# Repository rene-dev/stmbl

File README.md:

Build Log: https://travis-ci.org/rene-dev/stmbl

DISCLAIMER
===

THE AUTHORS OF THIS SOFTWARE ACCEPT ABSOLUTELY NO LIABILITY FOR
ANY HARM OR LOSS RESULTING FROM ITS USE.  IT IS _EXTREMELY_ UNWISE
TO RELY ON SOFTWARE ALONE FOR SAFETY.  Any machinery capable of
harming persons must have provisions for completely removing power
from all motors, etc, before persons enter any danger area.  All
machinery must be designed to comply with local and national safety
codes, and the authors of this software can not, and do not, take
any responsibility for such compliance.

This software is released under the GPLv3.

STMBL
=====
There is work in progress on documentation: https://github.com/rene-dev/stmbl/blob/master/docs/src/Getting%20Started.adoc

**IRC: #stmbl on irc.hackint.eu**
https://webirc.hackint.org/#stmbl

STMBL is an open source servo drive designed for Retrofitting CNC machines and Robots. It supports Industrial AC and DC servos with up to 320V and 2kW (see [specs](https://github.com/rene-dev/stmbl/wiki/specs) for details).

Documentation about the PCB and pinout of the feedback connector:

https://github.com/rene-dev/stmbl/wiki/Pinouts

https://github.com/rene-dev/stmbl/wiki/PCB

##### Hardware version 4.1

##### Driving a Bosch Turboscara
https://www.youtube.com/watch?v=d6NH1W7DUnQ  
https://www.youtube.com/watch?v=oTllxnYAgFc

##### Driving a Manutec Robot
https://www.youtube.com/watch?v=gwgnAeGjZrA  
https://www.youtube.com/watch?v=wXLcAZwjlzE

##### Driving a Weeke BP12 VMC
https://www.youtube.com/watch?v=24LftGNp4MI

##### Driving a Haas VF0 (Spindle + Axes)
https://www.youtube.com/watch?v=kqenepupJIs

##### Drivetest
https://www.youtube.com/watch?v=-E1o_5cFyto

#### Supported Motors
* Synchronous AC Servos
* Asynchronous AC Servos
* DC Servos
* 2 Phase HF spindle motors

#### Supported Feedback systems
* Resolvers
* Incremental encoders
* sin/cos encoder interpolation
* Mitsubishi absolute encoders
* Sanyo Denki absolute encoders
* Yaskawa absolute encoders
* Sick HIPERFACE®
* Tamagawa SmartAbs

##### Planned:
* EnDat
* BiSS
* SSI
* Sanyo Denki wire-saving incremental encoder

#### Supported Position/Velocity Commands Inputs:
* Smartserial
* Quadrature
* Step/direction
* RS485

#### TODO
* Sensorless FOC

#### Directories
* [hw/spice/](hw/spice/) Spice simulation for resolver interface
* [hw/kicad/v4.0/](hw/kicad/v4.0/) kicad files for version 4
* [src/](src/) STM32F4 code, command, feedback and control loop
* [stm32f303/](stm32f303/) STM32F3 code, running on the HV side, generating PWM

##### Commercial Applications

Should you find the GPL license insufficient for your needs, other licenses
can be purchased from my company.

Likewise, please contact us should you wish to fund the further development
of this project, or are interesed in custom hardware, software, or commercial support.

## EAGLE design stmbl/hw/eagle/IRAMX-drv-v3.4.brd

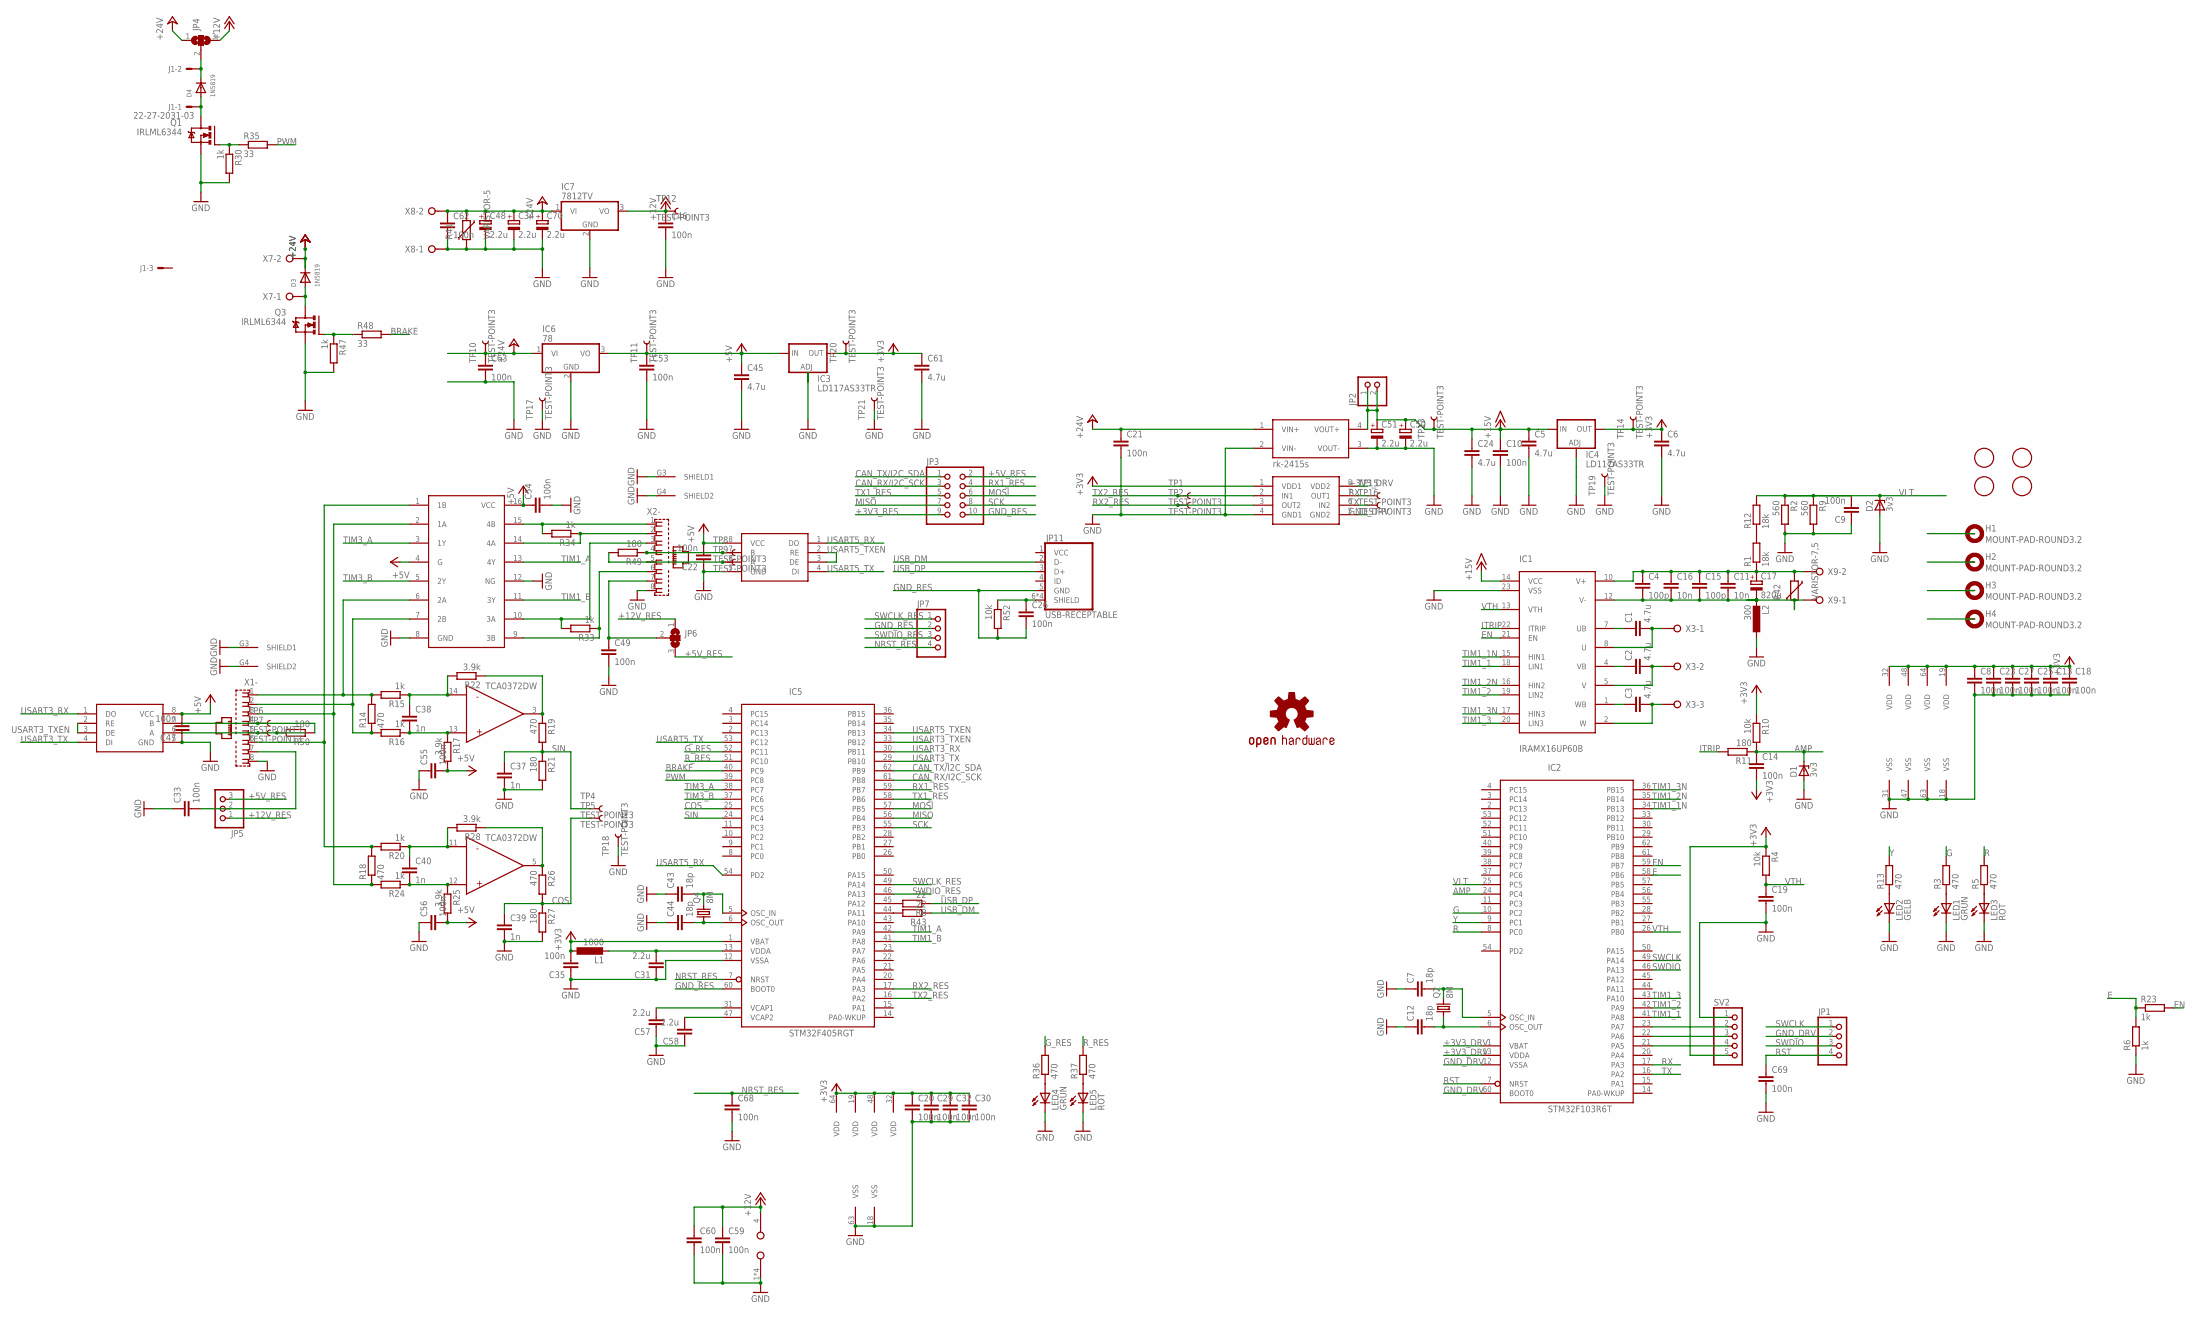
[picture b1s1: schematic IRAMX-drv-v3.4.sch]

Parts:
C1, C2, C3, C5, C6, C24, C45, C61: 4.7u; C0805
C4, C15: 100p; C1206K
C7, C12, C43, C44: 18p; C0603
C8, C9, C10, C13, C14, C18, C19, C20, C21, C22, C23, C25, C26, C27, C29, C30, C32, C33, C35, C46, C47, C49, C53, C54, C55, C56, C59, C60, C62, C63, C68, C69: 100n; C0603
C11, C16: 10n; C1206K
C17: 820µ; EB35D
C31, C57, C58: 2.2u; C0603
C34, C50, C70: 2.2u; 153CLV-0405
C37, C38, C39, C40: 1n; C0603
C48, C51: 2.2u; E2,5-6E
D1, D2: 3v3; SOD80C
D3, D4: 1N5819; SOD-123
H1, H2, H3, H4: MOUNT-PAD-ROUND3.2; 3,2-PAD
IC1: IRAMX16UP60B; SIP23_TOP
IC2: STM32F103R6T; LQFP64
IC3, IC4: LD117AS33TR; SOT223
IC5: STM32F405RGT; LQFP64
IC6: 78; R-78E
IC7: 7812TV; TO220V
IC8, IC9: ADM485SOIC8; SOIC08
IC10: TCA0372DWDM2; TCA0372DM2
IC12: SI8621; SOIC08
IC13: AM26LS32ACD; SO16
IC14: rk-2415s; SIP7
J1: 22-27-2031-03; 6410-03
JP1, JP7: PINHD-1X4; 1X04
JP2: PINHD-1X2; 1X02
JP3: PINHD-2X5; 2X05
JP4, JP6: SJ2W; SJ_2
JP5: PINHD-1X3; 1X03
JP11: USB-RECEPTABLE; FCI-10103594-0001LF
L1: 1000; L2825P
L2: 300; L2825P
LED1, LED4: GRÜN; LED3MM
LED2: GELB; LED3MM
LED3, LED5: ROT; LED3MM
LOGO1: OSHW-LOGOL; OSHW-LOGO-L
Q1, Q3: IRLML6344; MICRO3
Q2, Q4: 8M; CTS406
R1, R12: 18k; CER
R2, R9: 560; R0805
R3, R5, R13, R14, R18, R19, R26, R36, R37: 470; R0603
R4, R10, R52: 10k; R0603
R6, R15, R16, R20, R23, R24, R30, R33, R34, R47: 1k; R0603
R8, R43: 22; R0603
R11, R21, R27, R49, R50: 180; R0603
R17, R22, R25, R28: 3.9k; R0603
R35, R48: 33; R0603
R41: VARISTOR-5; R-5
R42: VARISTOR-7,5; R-7,5
SV2: PINHD-1X5; 1X05
TP1, TP2, TP4, TP5, TP6, TP7, TP8, TP9, TP10, TP11, TP12, TP13, TP14, TP15, TP16, TP17, TP18, TP19, TP20, TP21: TEST-POINT3; PAD.03X.03
U$8, U$9, U$10, U$11: FIDUCIAL; FIDUCIAL_1MM
X1, X2: RJ45
X3: AKL230-03
X7, X8, X9: AKL230-02

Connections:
+3V3_DRV: C6.1, C8.1, C13.1, C14.2, C18.1, C23.1, C25.1, C27.1, IC2.1 (VBAT), IC2.13 (VDDA), IC2.19 (VDD), IC2.32 (VDD), IC2.48 (VDD), IC2.64 (VDD), IC4.2 (OUT), IC4.4 (OUT), IC12.8 (VDD2), R4.1, R10.1, SV2.5, TP14.P$1
+3V3_RES: C20.1, C29.1, C30.1, C32.1, C35.2, C61.1, IC3.2 (OUT), IC3.4 (OUT), IC5.1 (VBAT), IC5.19 (VDD), IC5.32 (VDD), IC5.48 (VDD), IC5.64 (VDD), IC12.1 (VDD1), JP3.9, L1.1, TP20.P$1
+5V_RES: C22.2, C45.1, C47.2, C53.1, C54.1, C55.2, C56.2, IC3.3 (IN), IC6.3 (VO), IC8.8 (VCC), IC9.8 (VCC), IC13.4 (G), IC13.16 (VCC), JP3.2, JP5.3, JP6.3, R17.2, R25.2, TP11.P$1
+12V_RES: C46.1, C59.1, C60.1, IC7.3 (VO), IC10.4 (VCC), JP4.3, JP5.1, JP6.1, TP12.P$1
+15V_DRV: C5.1, C10.1, C24.1, C50.+, C51.+, IC1.14 (VCC), IC4.3 (IN), IC14.4 (VOUT+), JP2.1, JP2.2, TP13.P$1
+24V_RES: C21.1, C34.+, C48.+, C62.1, C63.1, C70.+, D3.C, IC6.1 (VI), IC7.1 (VI), IC14.1 (VIN+), JP4.1, R41.1, TP10.P$1, X7.2, X8.2
AMP: C14.1, D1.C, IC2.24 (PC4), R10.2, R11.1
BRAKE: IC5.40 (PC9), R48.2
CAN_RX/I2C_SCK: IC5.61 (PB8), JP3.3
CAN_TX/I2C_SDA: IC5.62 (PB9), JP3.1
COS: C39.1, IC5.25 (PC5), R26.2, R27.1, TP5.P$1
E: IC2.58 (PB6), R6.2, R23.1
EN: IC1.21 (EN), IC2.59 (PB7), R23.2
G: IC2.10 (PC2), R3.2
GND_DRV: C5.2, C6.2, C7.1, C8.2, C9.1, C10.2, C12.1, C13.2, C18.2, C19.2, C23.2, C24.2, C25.2, C27.2, C50.-, C51.-, C69.2, D1.A, D2.A, IC1.23 (VSS), IC2.12 (VSSA), IC2.18 (VSS), IC2.31 (VSS), IC2.47 (VSS), IC2.60 (BOOT0), IC2.63 (VSS), IC4.1 (ADJ), IC12.5 (GND2), IC14.3 (VOUT-), JP1.2, L2.1, LED1.K (C), LED2.K (C), LED3.K (C), R2.2, R6.1, R9.2, SV2.1, TP19.P$1
GND_RES: C20.2, C21.2, C22.1, C26.2, C29.2, C30.2, C31.1, C32.2, C33.1, C34.-, C35.1, C37.2, C39.2, C43.1, C44.1, C45.2, C46.2, C47.1, C48.-, C49.2, C53.2, C54.2, C55.1, C56.1, C57.1, C58.1, C59.2, C60.2, C61.2, C62.2, C63.2, C68.2, C70.-, IC3.1 (ADJ), IC5.12 (VSSA), IC5.18 (VSS), IC5.60 (BOOT0), IC5.63 (VSS), IC6.2 (GND), IC7.2 (GND), IC8.5 (GND), IC9.5 (GND), IC10.1 (GND), IC10.8 (GND), IC10.9 (GND), IC10.16 (GND), IC12.4 (GND1), IC13.8 (GND), IC13.12 (NG), IC14.2 (VIN-), JP3.10, JP7.2, JP11.5 (GND), LED4.K (C), LED5.K (C), Q1.2 (S), Q3.2 (S), R21.2, R27.2, R30.2, R41.2, R47.2, R52.2, TP17.P$1, TP18.P$1, TP21.P$1, X1.8, X1.G3 (SHIELD1), X1.G4 (SHIELD2), X2.8, X2.G3 (SHIELD1), X2.G4 (SHIELD2), X8.1
G_RES: IC5.52 (PC11), R36.2
ITRIP: IC1.22 (ITRIP), R11.2
MISO: IC5.56 (PB4), JP3.7
MOSI: IC5.57 (PB5), JP3.6
unnamed: C1.1, IC1.7 (UB)
unnamed: R1.P$2 (2), R12.P$1 (1)
unnamed: C2.1, IC1.4 (VB)
unnamed: C3.1, IC1.1 (WB)
unnamed: LED1.A, R3.1
unnamed: LED3.A, R5.1
unnamed: C7.2, IC2.5 (OSC_IN), Q2.3 (2)
unnamed: LED4.A, R36.1
unnamed: C12.2, IC2.6 (OSC_OUT), Q2.1
unnamed: C33.2, JP5.2, X1.7
unnamed: IC10.3 (OUT), R19.1, R22.1
unnamed: C38.2, IC10.13 (IN+), R16.1, R17.1
unnamed: LED5.A, R37.1
unnamed: C40.2, IC10.12 (IN+), R24.1, R25.1
unnamed: C49.1, JP6.2, X2.7
unnamed: IC10.5 (OUT), R26.1, R28.1
unnamed: IC9.7 (B), R50.1, TP6.P$1, X1.4
unnamed: C40.1, IC10.11 (IN-), R20.1, R28.2
unnamed: IC13.15 (4B), R34.2, X2.1
unnamed: C38.1, IC10.14 (IN-), R15.1, R22.2
unnamed: IC9.6 (A), R50.2, TP7.P$1, X1.5
unnamed: IC13.14 (4A), R34.1, X2.2
unnamed: IC13.10 (3A), R33.2, X2.3
unnamed: IC13.9 (3B), R33.1, X2.6
unnamed: IC13.1 (1B), R18.2, R20.2, X1.6
unnamed: IC13.7 (2B), R14.1, R16.2, X1.2
unnamed: D4.A, J1.1, Q1.3 (D)
unnamed: LED2.A, R13.1
unnamed: Q1.1 (G), R30.1, R35.1
unnamed: IC13.6 (2A), R14.2, R15.2, X1.1
unnamed: IC13.2 (1A), R18.1, R24.2, X1.3
unnamed: D4.C, J1.2, JP4.2
unnamed: IC8.6 (A), R49.2, TP9.P$1, X2.5
unnamed: IC8.7 (B), R49.1, TP8.P$1, X2.4
unnamed: D3.A, Q3.3 (D), X7.1
unnamed: Q3.1 (G), R47.1, R48.1
NRST_RES: C68.1, IC5.7 (NRST), JP7.4
OSC_IN: C43.2, IC5.5 (OSC_IN), Q4.3 (2)
OSC_OUT: C44.2, IC5.6 (OSC_OUT), Q4.1
PA5: IC2.21 (PA5), SV2.4
PA6: IC2.22 (PA6), SV2.3
PA7: IC2.23 (PA7), SV2.2
PWM: IC5.39 (PC8), R35.2
R: IC2.8 (PC0), R5.2
RST: C69.1, IC2.7 (NRST), JP1.4
RX: IC2.17 (PA3), IC12.7 (OUT1), TP15.P$1
RX1_RES: IC5.59 (PB7), JP3.4
RX2_RES: IC5.17 (PA3), IC12.3 (OUT2), TP2.P$1
R_RES: IC5.51 (PC10), R37.2
SCK: IC5.55 (PB3), JP3.8
SIN: C37.1, IC5.24 (PC4), R19.2, R21.1, TP4.P$1
SWCLK: IC2.49 (PA14), JP1.1
SWCLK_RES: IC5.49 (PA14), JP7.1
SWDIO: IC2.46 (PA13), JP1.3
SWDIO_RES: IC5.46 (PA13), JP7.3
TIM1_1: IC1.18 (LIN1), IC2.41 (PA8)
TIM1_1N: IC1.15 (HIN1), IC2.34 (PB13)
TIM1_2: IC1.19 (LIN2), IC2.42 (PA9)
TIM1_2N: IC1.16 (HIN2), IC2.35 (PB14)
TIM1_3: IC1.20 (LIN3), IC2.43 (PA10)
TIM1_3N: IC1.17 (HIN3), IC2.36 (PB15)
TIM1_A: IC5.42 (PA9), IC13.13 (4Y)
TIM1_B: IC5.41 (PA8), IC13.11 (3Y)
TIM3_A: IC5.38 (PC7), IC13.3 (1Y)
TIM3_B: IC5.37 (PC6), IC13.5 (2Y)
TX: IC2.16 (PA2), IC12.6 (IN2), TP16.P$1
TX1_RES: IC5.58 (PB6), JP3.5
TX2_RES: IC5.16 (PA2), IC12.2 (IN1), TP1.P$1
U: C1.2, IC1.8 (U), X3.1
USART3_RX: IC5.30 (PB11), IC9.1 (DO)
USART3_TX: IC5.29 (PB10), IC9.4 (DI)
USART3_TXEN: IC5.33 (PB12), IC9.2 (RE), IC9.3 (DE)
USART5_RX: IC5.54 (PD2), IC8.1 (DO)
USART5_TX: IC5.53 (PC12), IC8.4 (DI)
USART5_TXEN: IC5.34 (PB13), IC8.2 (RE), IC8.3 (DE)
USB_DM: JP11.2 (D-), R43.1
USB_DM_: IC5.44 (PA11), R43.2
USB_DP: JP11.3 (D+), R8.1
USB_DP_: IC5.45 (PA12), R8.2
USB_SHIELD: C26.1, JP11.6 (SHIELD), JP11.7 (SHIELD), JP11.8 (SHIELD), JP11.9 (SHIELD), R52.1
V: C2.2, IC1.5 (V), X3.2
V+: C4.1, C11.1, C15.1, C16.1, C17.+, IC1.10 (V+), R1.P$1 (1), R42.1, X9.2
V-: C4.2, C11.2, C15.2, C16.2, C17.-, IC1.12 (V-), L2.2, R42.2, X9.1
VCAP1: C57.2, IC5.31 (VCAP1)
VCAP2: C58.2, IC5.47 (VCAP2)
VDDA: C31.2, IC5.13 (VDDA), L1.2
VLT: C9.2, D2.C, IC2.25 (PC5), R2.1, R9.1, R12.P$2 (2)
VTH: C19.1, IC1.13 (VTH), IC2.26 (PB0), R4.2
W: C3.2, IC1.2 (W), X3.3
Y: IC2.9 (PC1), R13.2

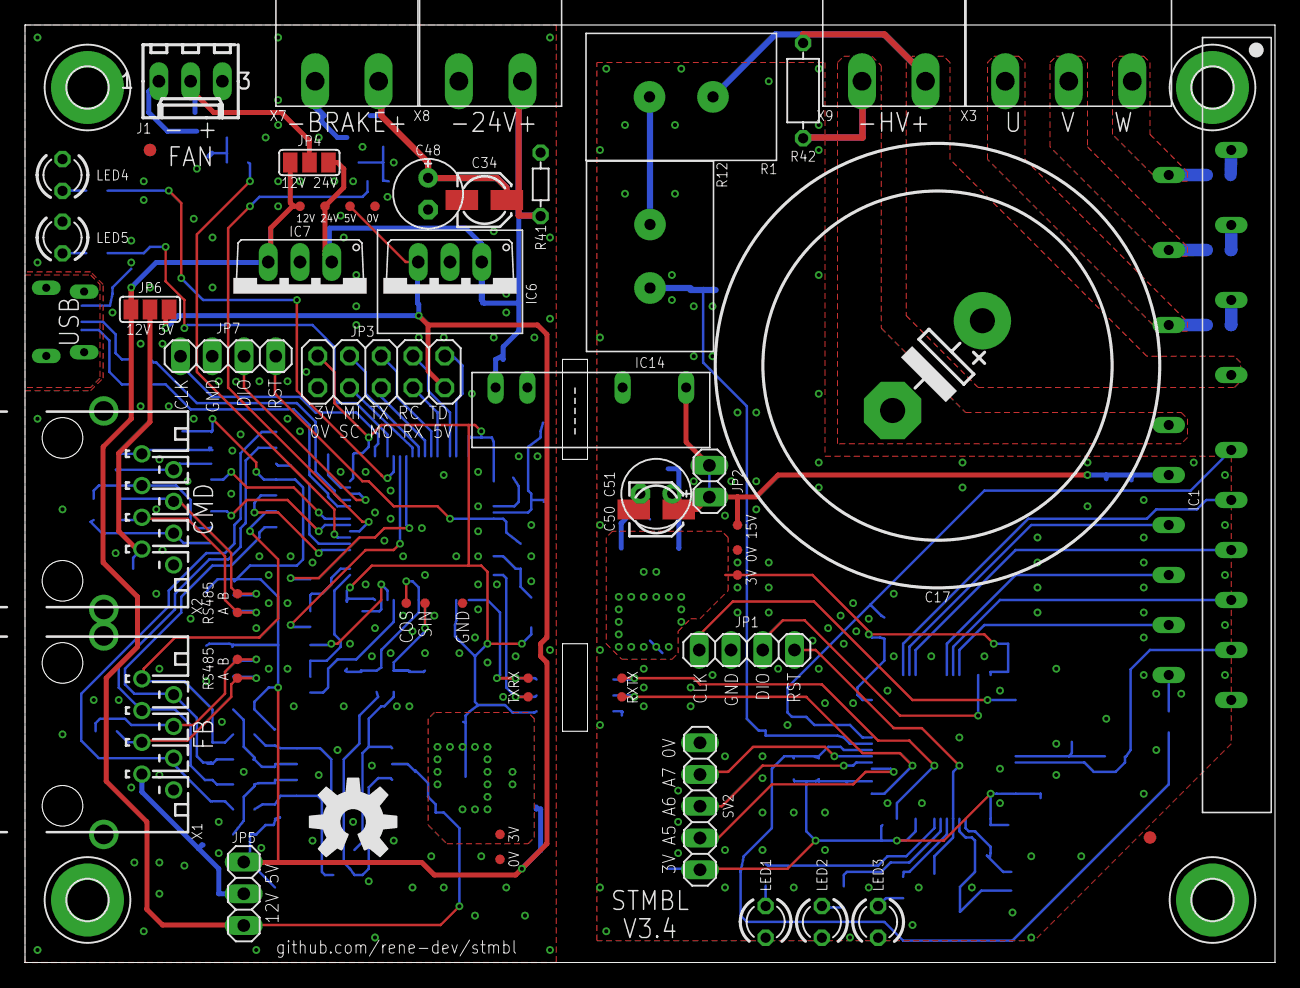
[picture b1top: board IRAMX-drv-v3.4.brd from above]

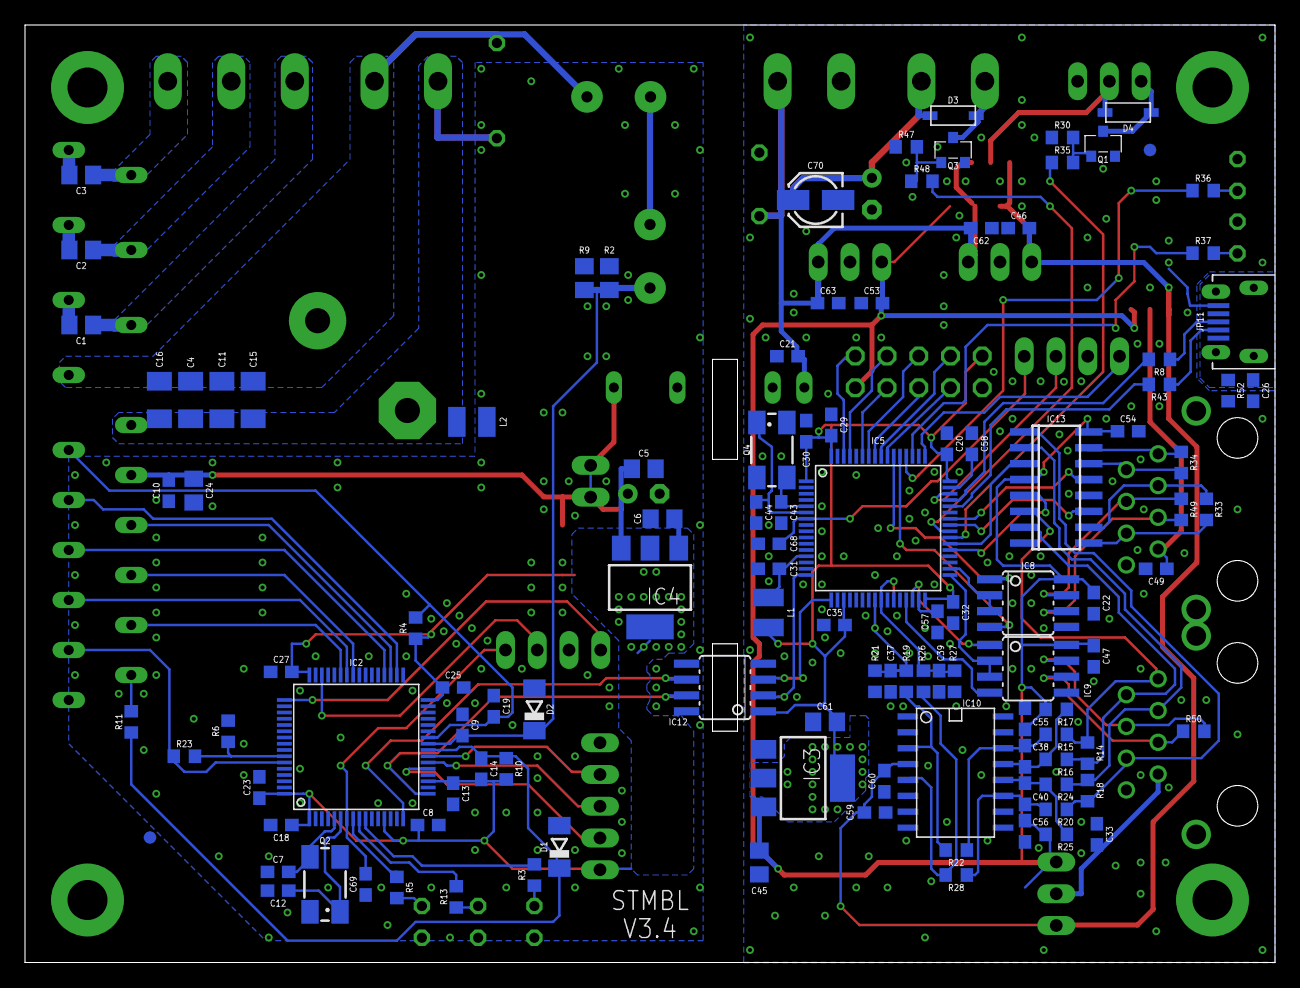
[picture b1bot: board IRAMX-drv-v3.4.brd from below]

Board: 2 copper layers, 100.0 x 75.0 mm, 175 parts (115 on the bottom side), 110 nets.

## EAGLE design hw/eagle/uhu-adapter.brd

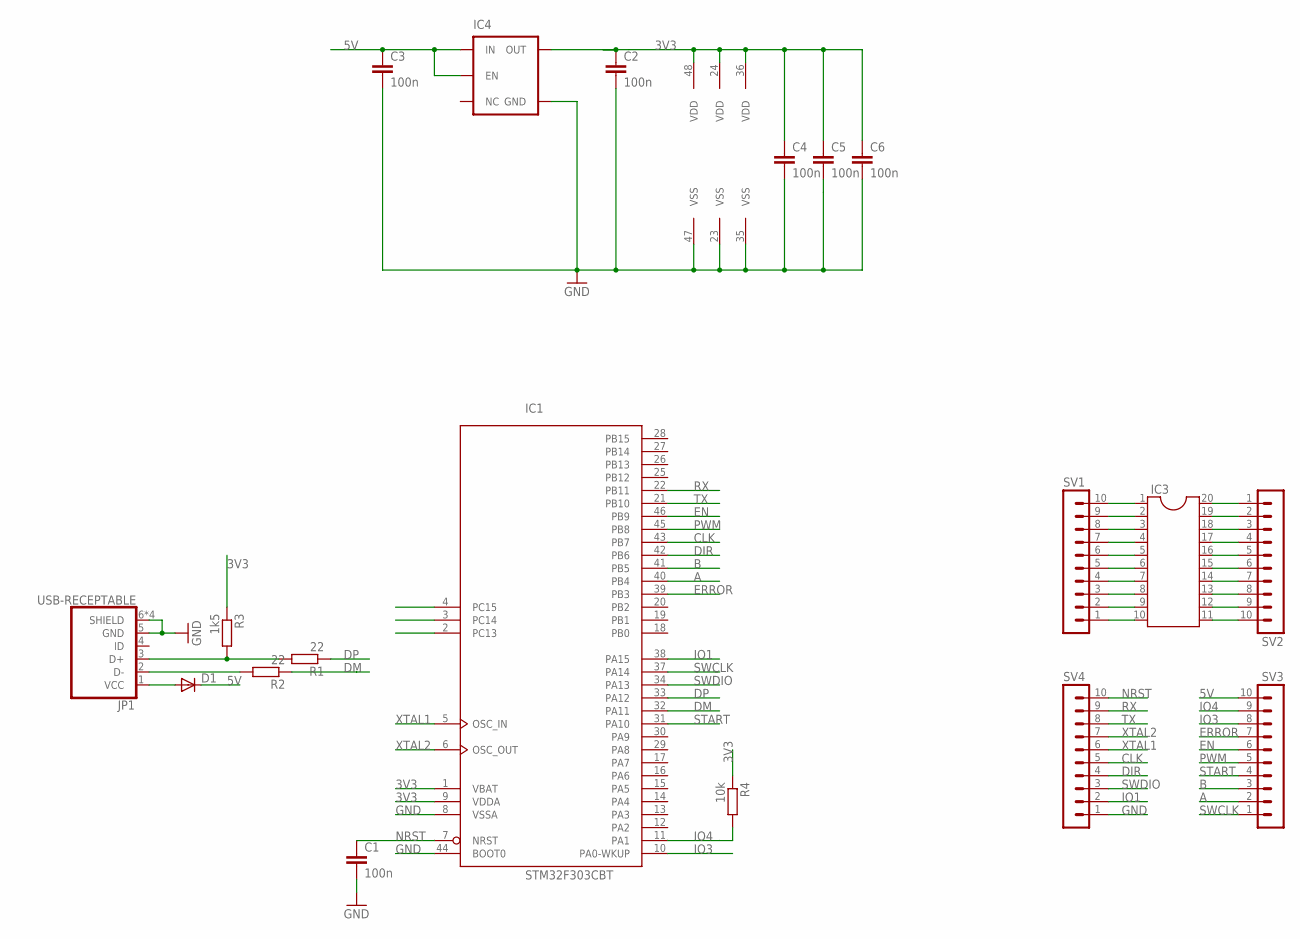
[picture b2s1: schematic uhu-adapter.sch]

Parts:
C1, C2, C3, C4, C5, C6: 100n; C0603
D1: DIODE-SOD123; SOD123
IC1: STM32F303CBT; LQFP48
IC3: DIL20
IC4: V_REG_TPS76433SOT23-5; SOT23-5
JP1: USB-RECEPTABLE; FCI-10103594-0001LF
R1, R2: 22; R0603
R3: 1k5; R0603
R4: 10k; R0603
SV1, SV2, SV3, SV4: MA10-1

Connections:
3V3: C2.1, C4.1, C5.1, C6.1, IC1.1 (VBAT), IC1.9 (VDDA), IC1.24 (VDD), IC1.36 (VDD), IC1.48 (VDD), IC4.5 (OUT), R3.1, R4.1
5V: C3.1, D1.C, IC4.1 (IN), IC4.3 (EN), SV3.10
5VUSB: D1.A, JP1.1 (VCC)
A: IC1.40 (PB4), SV3.2
B: IC1.41 (PB5), SV3.3
CLK: IC1.43 (PB7), SV4.5
DIR: IC1.42 (PB6), SV4.4
DM: IC1.32 (PA11), R2.1
DP: IC1.33 (PA12), R1.1
EN: IC1.46 (PB9), SV3.6
ERROR: IC1.39 (PB3), SV3.7
GND: C1.2, C2.2, C3.2, C4.2, C5.2, C6.2, IC1.8 (VSSA), IC1.23 (VSS), IC1.35 (VSS), IC1.44 (BOOT0), IC1.47 (VSS), IC4.2 (GND), JP1.5 (GND), JP1.6 (SHIELD), JP1.7 (SHIELD), JP1.8 (SHIELD), JP1.9 (SHIELD), SV4.1
IO1: IC1.38 (PA15), SV4.2
IO3: IC1.10 (PA0-WKUP), SV3.8
IO4: IC1.11 (PA1), R4.2, SV3.9
unnamed: IC3.10, SV1.1
unnamed: IC3.9, SV1.2
unnamed: IC3.8, SV1.3
unnamed: IC3.7, SV1.4
unnamed: IC3.6, SV1.5
unnamed: IC3.5, SV1.6
unnamed: IC3.4, SV1.7
unnamed: IC3.3, SV1.8
unnamed: IC3.2, SV1.9
unnamed: IC3.1, SV1.10
unnamed: IC3.20, SV2.1
unnamed: IC3.19, SV2.2
unnamed: IC3.18, SV2.3
unnamed: IC3.17, SV2.4
unnamed: IC3.16, SV2.5
unnamed: IC3.15, SV2.6
unnamed: IC3.14, SV2.7
unnamed: IC3.13, SV2.8
unnamed: IC3.12, SV2.9
unnamed: IC3.11, SV2.10
unnamed: JP1.3 (D+), R1.2, R3.2
unnamed: JP1.2 (D-), R2.2
NRST: C1.1, IC1.7 (NRST), SV4.10
PWM: IC1.45 (PB8), SV3.5
RX: IC1.22 (PB11), SV4.9
START: IC1.31 (PA10), SV3.4
SWCLK: IC1.37 (PA14), SV3.1
SWDIO: IC1.34 (PA13), SV4.3
TX: IC1.21 (PB10), SV4.8
XTAL1: IC1.5 (OSC_IN), SV4.6
XTAL2: IC1.6 (OSC_OUT), SV4.7

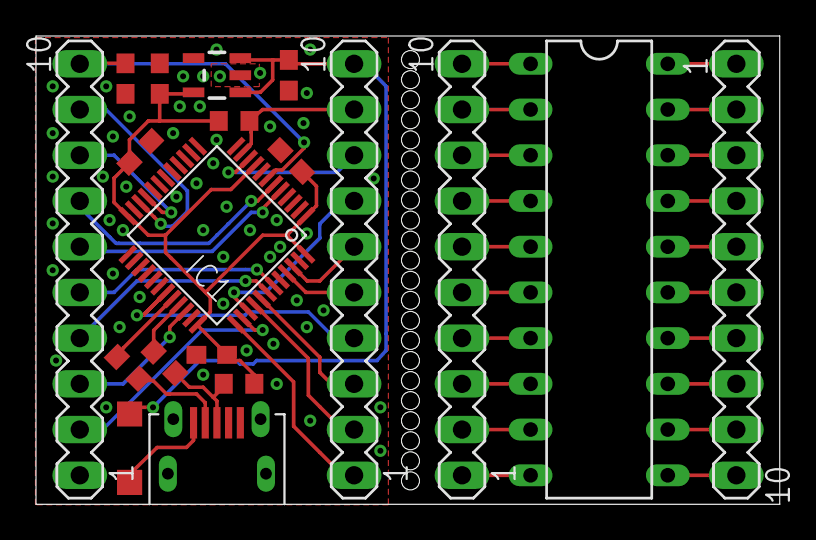
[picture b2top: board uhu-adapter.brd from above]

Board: 2 copper layers, 41.3 x 26.0 mm, 19 parts (0 on the bottom side), 46 nets.

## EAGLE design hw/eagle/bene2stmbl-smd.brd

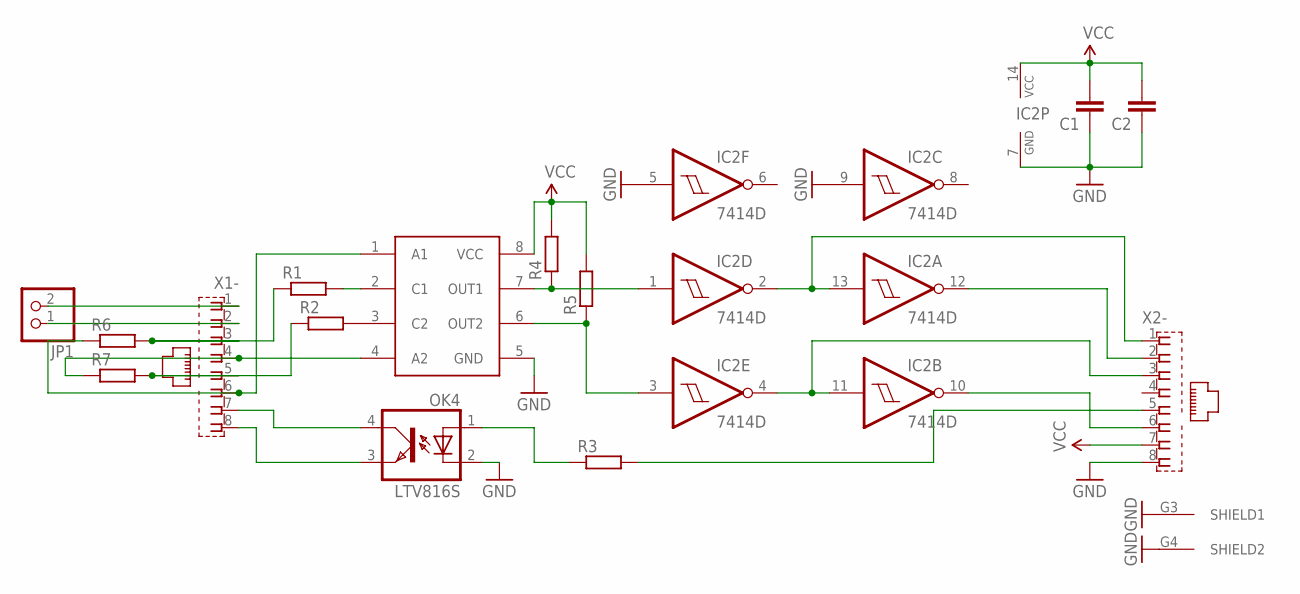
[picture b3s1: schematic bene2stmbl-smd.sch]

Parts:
C1, C2: C-EUC0603; C0603
IC2: 7414D; SO14
JP1: PINHD-1X2; 1X02
OK4: LTV816S; SMD4
R1, R2, R3, R4, R5, R6, R7: R-EU_R0603; R0603
U$1: HCPL-053L-SMD; SO08
X1, X2: RJ45

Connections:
GND: C1.1, C2.1, IC2.5 (I), IC2.7 (GND), IC2.9 (I), OK4.2 (C), U$1.5 (GND), X2.8, X2.G3 (SHIELD1), X2.G4 (SHIELD2)
unnamed: OK4.3 (EMIT), X1.8
unnamed: OK4.4 (COL), X1.7
unnamed: IC2.2 (O), IC2.13 (I), X2.1
unnamed: R6.1, U$1.1 (A1), X1.6
unnamed: IC2.4 (O), IC2.11 (I), X2.3
unnamed: R2.1, R7.2, X1.5
unnamed: R1.2, U$1.2 (C1)
unnamed: R2.2, U$1.3 (C2)
unnamed: JP1.1, X1.2
unnamed: JP1.2, X1.1
unnamed: IC2.1 (I), R4.1, U$1.7 (OUT1)
unnamed: IC2.12 (O), X2.2
unnamed: R1.1, R6.2, X1.3
unnamed: IC2.10 (O), X2.6
unnamed: OK4.1 (A), R3.1
unnamed: R7.1, U$1.4 (A2), X1.4
unnamed: R3.2, X2.5
unnamed: IC2.3 (I), R5.1, U$1.6 (OUT2)
VCC: C1.2, C2.2, IC2.14 (VCC), R4.2, R5.2, U$1.8 (VCC), X2.7

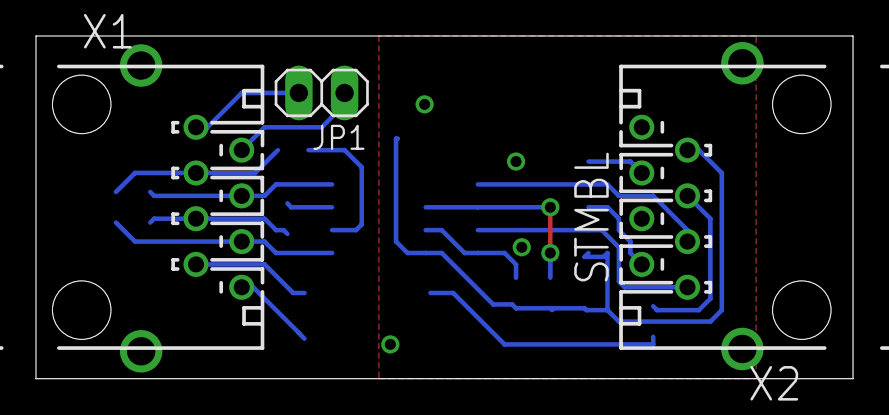
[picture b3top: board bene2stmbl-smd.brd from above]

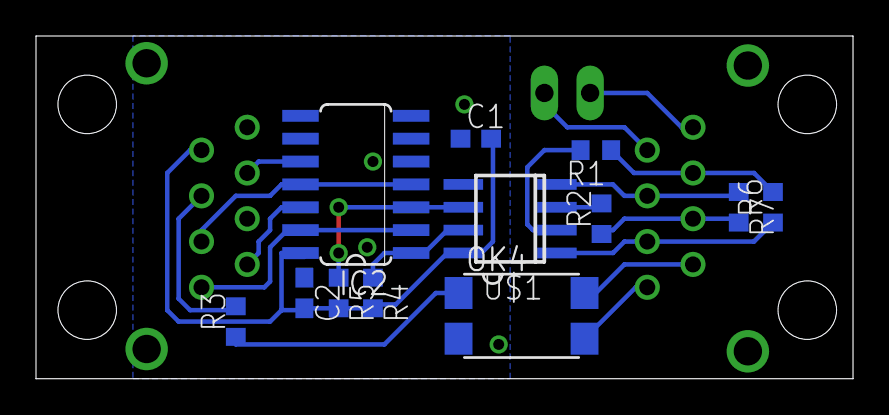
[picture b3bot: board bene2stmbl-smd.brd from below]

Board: 2 copper layers, 45.4 x 19.0 mm, 15 parts (12 on the bottom side), 20 nets.

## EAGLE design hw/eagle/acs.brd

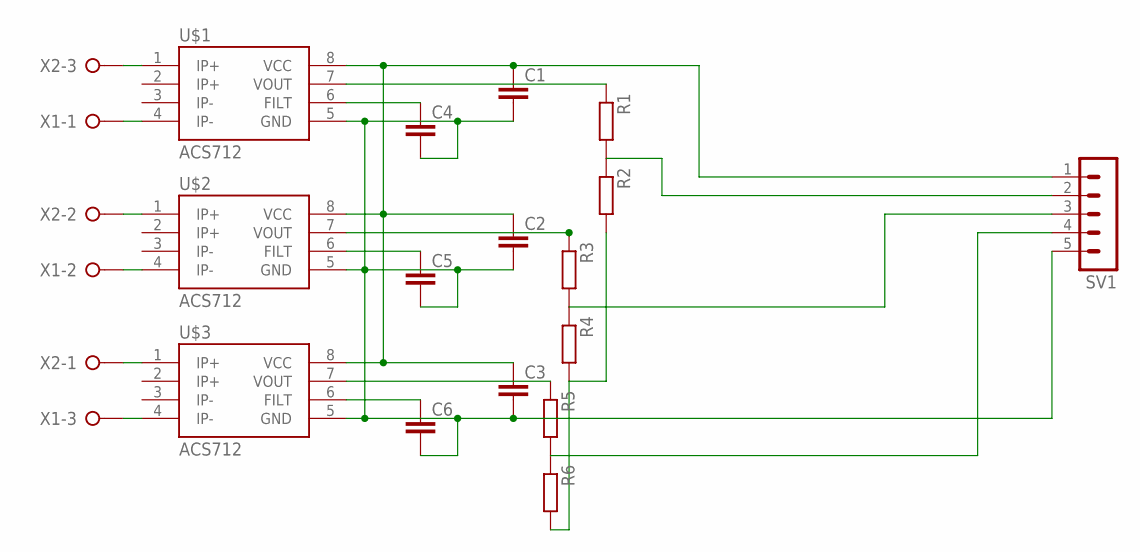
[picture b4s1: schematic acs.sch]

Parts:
C1, C2, C3, C4, C5, C6: C-EUC0603; C0603
R1, R2, R3, R4, R5, R6: R-EU_R0603; R0603
SV1: MA05-1
U$1, U$2, U$3: ACS712; SO08
X1, X2: W237-03P; W237-133

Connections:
unnamed: U$1.4 (IP-), X1.1
unnamed: U$1.1 (IP+), X2.3
unnamed: U$2.4 (IP-), X1.2
unnamed: U$2.1 (IP+), X2.2
unnamed: U$3.1 (IP+), X2.1
unnamed: U$3.4 (IP-), X1.3
unnamed: C1.1, C2.1, C3.1, SV1.1, U$1.8 (VCC), U$2.8 (VCC), U$3.8 (VCC)
unnamed: C1.2, C2.2, C3.2, C4.2, C5.2, C6.2, SV1.5, U$1.5 (GND), U$2.5 (GND), U$3.5 (GND)
unnamed: C4.1, U$1.6 (FILT)
unnamed: C5.1, U$2.6 (FILT)
unnamed: C6.1, U$3.6 (FILT)
unnamed: R1.2, R2.1, SV1.2
unnamed: R1.1, U$1.7 (VOUT)
unnamed: R3.1, U$2.7 (VOUT)
unnamed: R5.1, U$3.7 (VOUT)
unnamed: R3.2, R4.1, SV1.3
unnamed: R5.2, R6.1, SV1.4
unnamed: R2.2, R4.2, R6.2

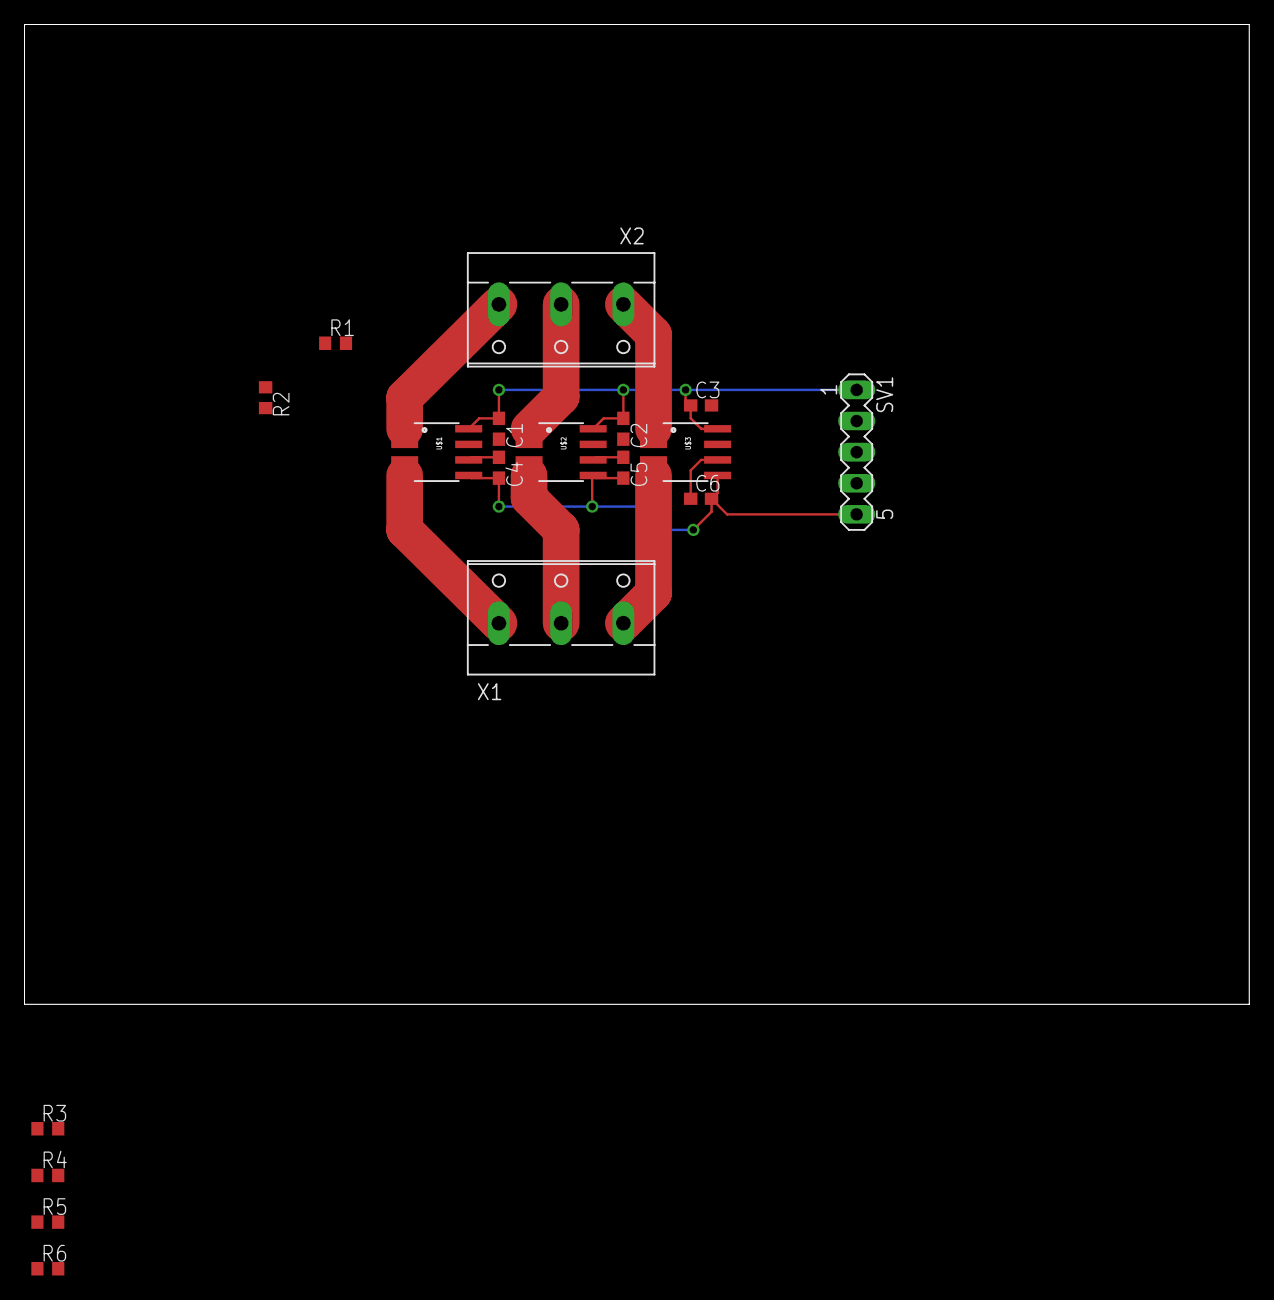
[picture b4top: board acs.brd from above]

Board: 2 copper layers, 100.0 x 80.0 mm, 18 parts (0 on the bottom side), 18 nets.

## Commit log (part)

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2018-03-25 fanuc encoder request via spi, led, error
2018-03-25 fanuc request time
2018-03-25 frequency
2018-03-25 abspos
2018-03-25 fanuc abs pos fix
2018-03-25 com test fix
2018-03-29 Change Command Connector pin description
    Added Enable and Error pins
2018-03-29 fix pinouts
2018-03-29 Update Getting Started.adoc
    Add Brushless UVW sensors for use by fb1
2018-03-30 fanuc crc
2018-03-31 sserial dummy template
2018-04-01 added input pin for cmd pair 7,8
2018-04-01 fix syntax
2018-04-01 adc dma buffer should be volatile
2018-04-01 dont fault on fault pin
2018-04-01 frt jitter by new hv sync now requires more blocking by sserial
2018-04-01 save last fault code
2018-04-01 fix build
2018-04-02 stmbl 4.2 wip
2018-04-02 update version
2018-04-03 stmbl 4.2 rc
2018-04-04 v4 sheet metal case wip
2018-04-04 kicad lib
2018-04-05 stmbl 4.2
2018-04-05 stmbl 4.2 bom
2018-04-05 stmbl 4.2 lib fix
2018-04-06 reslimit fix
2018-04-06 not comp
2018-04-06 f3 fault
2018-04-06 fix pwm clamping problem
2018-04-06 pragma fix, hv fault fix
2018-04-06 hv fault fix
2018-04-06 stmbltalk update, hv_update fix
2018-04-06 makefile hv firmware fix
2018-04-06 format
2018-04-07 python3 compatibility
2018-04-07 cleanup
2018-04-07 rexroth conf
2018-04-07 makefile cleanup
2018-04-07 pid template rev cleanup
2018-04-07 adc dma double buffer fix
2018-04-07 sserial format
2018-04-07 Update Getting Started.adoc
    Correct F3 boot flashing command
2018-04-09 makefile fixes, v0.9.15
2018-04-09 fix deploy
2018-04-09 conf cleanup
2018-04-10 commutation position advance in f3
2018-04-11 enc error fix, adc amp
2018-04-11 disable flto on f3
2018-04-11 change timeout faults to higest priority
2018-04-11 hv bootloader fix
2018-04-11 global version number
2018-04-11 more sizeof checks
2018-04-11 add version number include
2018-04-11 optional toolchain-user.mak include file
2018-04-12 hv com fix, ignore fault pin
2018-04-12 fault cleanup
2018-04-12 fix python3 style print
2018-04-13 f4 usb cleanup
2018-04-13 fix warnings when compiling with -Wimplicit-fallthrough
2018-04-13 create dfu files on deploy target
2018-04-13 uptime command
2018-04-13 production targets
2018-04-14 dfu bin files
2018-04-14 iwdg wip
2018-04-16 iwdg + flash working
2018-04-16 usb cleanup
2018-04-16 new bootloader trigger, iwdg start in bootloader
2018-04-16 trigger bootloader on all_btburn
2018-04-16 f3 cleanup
2018-04-17 hal pin reverse lookup
2018-04-17 hardfault + iwdg
2018-04-17 moved docs from wiki to ascidoc
2018-04-17 hal nan trap
2018-04-18 stmsp port
2018-04-20 stmsp working
2018-04-20 stmsp fix
2018-05-01 Update Getting Started.adoc
    Fix table formatting for special cable section
2018-05-03 Update Getting Started.adoc
    Update blink codes
2018-05-03 Update Getting Started.adoc
    Updates to flashing procedures and error flash codes
2018-05-06 cmd freq pll, conf template cleanup
2018-05-14 fix com test
2018-05-21 sheet metal case wip
2018-05-31 sheet metal case 0.8mm
2018-06-02 sheet metal case io 0.8mm
2018-06-15 sanyo denki
2018-06-19 v4 bom wip
2018-06-19 v4.3 bom
2018-06-20 v4.3
2018-06-22 changed sanyo encoder to timer input capture
2018-06-24 fb tracking
2018-06-24 ignore fault pin
2018-06-24 enc_cmd rempa, encs state
2018-06-24 bene
2018-07-05 Add MC33879A
2018-07-09 added ke0 cap footprint to stmbl lib
2018-07-22 enc cmd remap fix
2018-08-13 Rename psi.conf to psi.txt
2018-08-25 brk pin poc
2018-09-11 disable pos and sat error when it is 0
2018-09-11 ramp fix
2018-09-11 weiler spindle config
2018-09-16 hal sleep cmd
2018-09-16 dual mass pid
2018-09-16 weiler conf
2018-09-16 simple iit
2018-09-16 iit fix
2018-09-16 velbuf
2018-09-19 avg comp
2018-09-19 -warning
2018-09-20 velbuf conf
2018-09-20 cmd enc input filter
2018-09-20 conf
2018-10-04 added rj45 pins to sserial pinout
2018-10-04 sserial uf
2018-10-05 readme update
2018-10-05 endat test
2018-10-05 tamagawa smartabs
2018-10-23 smartabs
2018-12-03 0.9.18 release
2018-12-16 += debounce, wobl, veltopos
2018-12-16 fb_switch cmd offset disable
2018-12-16 moved init code of smartabs and mitsu from nrt init to hw init
2018-12-16 hardboot
2018-12-25 optional fast outputs
2018-12-25 wobl test config
2018-12-28 fb_switch conf fix
2018-12-28 typo
2018-12-28 new autophase algo
2019-01-03 change to single crystal
2019-01-16 io out pwm
2019-01-16 wobl
2019-01-17 fix curpid cur clamp oscilation
2019-02-06 haas spindle conf, iram min on fix
2019-02-08 curpid current limit fix
2019-02-08 uf ramp
2019-02-08 uf 2kw conf
2019-02-08 bene uf update
2019-02-13 hx711 driver
2019-02-13 add gain and offset to hx711
2019-02-14 stp v2
2019-02-22 add index for 11ua, change to lm339
2019-02-22 add rescue lib
2019-02-22 differential driver with index
2019-02-22 flip layout
2019-02-22 change over to 4 layer, change cpu to F7
2019-02-22 changed things
2019-02-22 add polymer caps and make zone more nicer
2019-02-22 now with three times the fun
2019-02-23 change rj45
2019-02-23 remove interp
2019-02-23 moved stuff around
2019-03-03 hx foo
2019-03-03 home
2019-03-14 change to opamp....
2019-03-14 unflip rj45 socket
2019-03-14 put connectors into separate file
2019-03-17 Update stp.c
    stp jog fix
2019-03-17 first commit of the baseboard for the netbob
2019-03-17 add outputs
2019-03-18 routing
2019-03-18 routing...
2019-03-18 RC0?
2019-03-19 add leds
2019-03-20 festo phase fix
2019-04-08 Spotted some typos and odd formatting
2019-04-29 cmd filter
2019-04-29 pos_filter en
2019-04-29 hal info print comp index, negative comp index search
2019-04-29 hal relink
2019-04-29 pos_filter template update
2019-04-29 hal pin single source lookup
2019-04-29 del hal volatile
2019-04-29 Update pos_filter.c
    mod fix
2019-04-29 mod fix
2019-05-01 rl measure foo
2019-05-01 hv voltage feedback
2019-05-01 rl e time
2019-05-01 rl conf
2019-05-07 posfilter
2019-05-07 pos_filter
2019-05-09 spindle pos + vel
2019-05-27 pid en fix
2019-05-27 ramp en fix
2019-05-29 sensorless
2019-06-03 acim foo
2019-06-05 acim
2019-06-27 acim fix
2019-06-27 gains
2019-06-29 endat wip
2019-06-29 endat
2019-06-29 drop, smith
2019-06-29 curpid fix
2019-06-29 rlpsij
2019-07-02 hw defines
2019-07-04 -drop
2019-10-24 finalize layout
2019-11-06 diff driver v2
2019-12-11 drop and move stuff
2019-12-12 move
2020-01-09 mask irq in smartabs
2020-01-16 cmd clock sync, hv in rt
2020-01-17 fanux fix
2020-01-26 fix encoder index capture
2020-02-20 hx711
2020-02-22 stuff
2020-02-23 wire saving
2020-02-24 hx, fmove
2020-02-24 hard stop homing
2020-03-04 Add alternative way to start servoterm in chrome
2020-03-14 add linuxcnc example config
2020-03-15 add wave tests
2020-03-17 removed html from terminal
2020-05-24 Update broken 3dshapes
    The KiCad library naming convention has changed over time and as a
    result many of the 3dshapes are not correctly referenced.
2020-07-09 fb_switch dual fb
2020-09-10 add dmm encoder support
2020-09-16 improved build time by having Python generated code preserve it's modification date when it's content isn't changing
2020-09-16 fixed Python file open mode
2020-09-16 fixed file_updater.py to work under python3
2020-09-20 disabled FileUpdater's behavior, it doesn't work with make the way it was intended
2020-09-20 fixed stm32f303/Makefile to only rebuild when necessary
2020-09-20 cleaned up use of .PHONY in Makefiles
2020-09-20 rewrote Makefile rules for Python generated code to only rebuild when necessary (FileUpdater is no longer required)
2020-09-20 fixed Makefile rule dependencies
2020-09-20 used Makefile variable where possible, and removed some debugging echo commands
2020-09-21 make -j works now
2020-09-22 made commandslist.h generation a dependency of only commands.o, improving rebuild time
2020-09-23 generate hader file / comp
2020-09-23 add comp header include
2020-09-23 comp include
2020-09-23 fixed comp Makefile dependencies to minimize recompiling
2020-09-23 removed unneeded Python script
2020-09-23 added missing create_comp_h.py script
2020-09-23 default python3
2020-09-27 removed need for file_updater.py
2020-10-10 new build system POC
2020-10-10 fix comps, -j
2020-10-10 ignore
2020-10-10 fix deps
2020-10-10 fix f4 wip
2020-10-12 f3 + f4 building
2020-10-12 fix flash
2020-10-12 fix gen stuff, working
2020-10-12 fix f3
2020-10-12 fix #comp
2020-10-12 fix cpu def
2020-11-01 fix build with gcc9
2020-11-01 warning about missing pyserial
2020-11-17 syscall fix
2020-11-17 python serial test
2020-11-17 shared app address for bootloader and makefile, force_lock fix
2020-11-17 move framework to submodule
2020-11-17 include framework submodule
2020-11-18 st_hal_f3 fix, optional opt flags, gitignore
2021-01-26 Fixed spelling error in hal_term_print_state function.
2021-04-14 C42-44 are working on 16V, 25V should do the job
2021-04-14 2.2uF caps 35V or 50V are unavailable on JLC PCBa
    Fixed LCSC # for 120 ohm 0603 resistor (was 1K2 one)
2021-04-14 We can use 1uF 50V 0603 for bypass caps, these are available on JLC
2021-05-24 add mitsu fd/hd switch, support different encoder version
2021-07-02 mitsu default cmd
2021-07-02 sys id + sim
2021-07-02 fix hv rev, sys id
2021-07-13 sys id, curpid bw, svm defalut mode
2021-07-14 -pmsm limits, pid -> bw, sys id
2021-07-27 Update Makefile
2021-08-26 auto id
2021-08-26 id doc
2021-08-26 id fix
2021-08-31 fix pid torque ff
2021-08-31 fix dc phasing
2021-09-10 smartabs crc
2021-09-11 idpmsm cmd_mode fix
2021-09-13 better defaults
2021-09-16 id stuff
2021-09-16 fix cmd acc ff
2021-09-16 improve doc
2021-09-17 new idm, improve doc, id_sys
2021-09-17 conf0.load
2021-09-17 stp standstill fix
2021-12-15 fix variable scope, multiple declerations error with gcc 10
2022-01-02 add missing crc
2022-04-26 print clamping warning

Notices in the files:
stmbl/f3/src/main.c:
Copyright (C) 2013-2017 Rene Hopf <renehopf@mac.com>
Copyright (C) 2013-2017 Nico Stute <crinq@crinq.de>
This program is free software: you can redistribute it and/or modify
it under the terms of the GNU General Public License as published by
the Free Software Foundation, either version 3 of the License, or
(at your option) any later version.
parts and their libraries:
SparkFun-Passives: Licensing: Creative Commons ShareAlike 4.0 International - https://creativecommons.org/licenses/by-sa/4.0
